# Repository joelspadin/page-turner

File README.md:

# Page Turner

This is an STM32-based "keyboard" which maps a pair of foot pedals with 6.35 mm (1/4") phone jacks to left/right arrow keys (or any other two keys), designed for switching pages on a sheet music reader. It was designed to be as small as possible while still being hand-solderable.

# PCB

The [pcb](./pcb) folder contains a [KiCad](https://www.kicad.org/) project for the PCB. It requires 4 layers and a 1.6 mm thick PCB.

All parts are hand-solderable. I recommend starting from the USB port and working out from the center on the top side, then soldering the phone jacks last.

With [Python](https://www.python.org/) and [Docker](https://www.docker.com/products/docker-desktop/) installed, you can use [KiBot](https://github.com/INTI-CMNB/KiBot) to generate Gerber files for JLC PCB or PCBWay. Simply run the [kibot.py](./kibot.py) script, then check the "out" folder for the results.

## Bill of Materials

| References | Part              | Manufacturer       | Package  | Qty. | Description           |
| ---------- | ----------------- | ------------------ | -------- | ---- | --------------------- |
| C5         | 10n capacitor     |                    | 0603     | 1    | SMT Ceramic capacitor |
| C3, C7     | 100n capacitor    |                    | 0603     | 2    | SMT Ceramic capacitor |
| C1, C2, C6 | 1u capacitor      |                    | 0603     | 3    | SMT Ceramic capacitor |
| C4         | 4.7u capacitor    |                    | 0603     | 1    | SMT Ceramic capacitor |
| R1, R2     | 5.1k resistor     |                    | 0603     | 2    | SMT resistor          |
| R3         | 10k resistor      |                    | 0603     | 1    | SMT resistor          |
| D1, D2     | SD03C-7           | Diodes Inc.        | SOD-323  | 2    | TVS diode             |
| D3         | PRTR5V0U2X,215    | Nexperia           | SOT-143  | 1    | TVS diode             |
| U1         | STM32F042F6P6TR   | STMicroelectronics | TSSOP-20 | 1    | ARM microcontroller   |
| U2         | TPS7A0533PDBVR    | Texas Instruments  | SOT-23-5 | 1    | 3.3V regulator        |
| SW1, SW2   | B3U-1000P-B       | Omron              |          | 2    | Tactile switch        |
| J1, J2     | NJ2FD-V           | Neutrik            |          | 2    | 6.35 mm phone jack    |
| J3         | USB4145-03-0170-C | GCT                |          | 1    | USB-C connector       |

D1, D2, and D3 are optional. They provide some ESD protection.

U2 may be substituted with any other 3.3V regulator that takes 5V input and uses the same footprint and pinout, e.g. TPS7A0333PDBVR.

# Firmware

The [src](./src) folder contains an Arduino sketch. It can be modified as necessary to change the two keys or if your foot pedals are normally closed instead of normally open.

You will need a SWD programmer such as a J-Link. I used a [Nordic nRF5340 DK](https://www.nordicsemi.com/Products/Development-hardware/nRF5340-DK). Other programmers such as a Black Magic Probe or STLink may work, but I have not tested these. Flashing instructions below assume using a J-Link.

There are pads for a Tag-Connect TC2030 "no legs" cable, or you can use the five pads at the top of the PCB to connect your programmer (note that these have 2 mm spacing instead of 2.54 mm due to size constraints).

To compile and flash the firmware:

1. Install [STM32CubeProgrammer](https://www.st.com/en/development-tools/stm32cubeprog.html)
2. Install and open [Arduino IDE](https://www.arduino.cc/en/software)
3. Install the [Arduino core for STM32](https://github.com/stm32duino/Arduino_Core_STM32/wiki/Getting-Started)
4. Open [src/page_turner.ino](./src/page_turner.ino) in Arduino IDE
5. Select **Tools > Board > STM32 MCU based boards > Generic STM32F0 series**
6. Select **Tools > Board part number > Generif F042F6Px**
7. Select **Tools > USB support (if available) > HID (keyboard and mouse)**
8. Select **Tools > Upload method > STM32CubeProgrammer (J-Link)**
9. Plug the PCB to USB power and connect your programmer to it.
10. Select **Sketch > Upload Using Programmer**

I ran into an issue where, after being flashed with Arduino firmware, STM32CubeProgrammer was unable to identify the board afterwards. To fix this, you can run STM32CubeProgrammer and try to connect. This will fail and ask you to select the type of processor. Select Cortex M0 to finish connecting. Run a full chip erase, then disconnect, and you will be able to flash again.

## Enclosure

The [enclosure](./enclosure) folder contains CAD files that can be used to create a 3D printed enclosure.

## Bill of Materials

| Part                                        | Qty. |
| ------------------------------------------- | ---- |
| [Back](./enclosure/Back.3mf) (3D printed)   | 1    |
| [Front](./enclosure/Front.3mf) (3D printed) | 1    |
| M2 x 3 mm heat-set insert                   | 4    |
| M2 x 5 mm counersunk screw                  | 4    |

## Assembly

1. Using a soldering iron, install the four heat set inserts into the holes in the back piece.

2. Place the PCB assembly into the back piece. The longer side of the PCB should line up with side of the back piece containing the heat-set inserts.

3. Press the caps into the 6.35 mm phone jacks and rotate them clockwise to lock them into place.
4. Slide the front piece on, lining up the four holes with the heat set inserts.

5. Install the four screws.

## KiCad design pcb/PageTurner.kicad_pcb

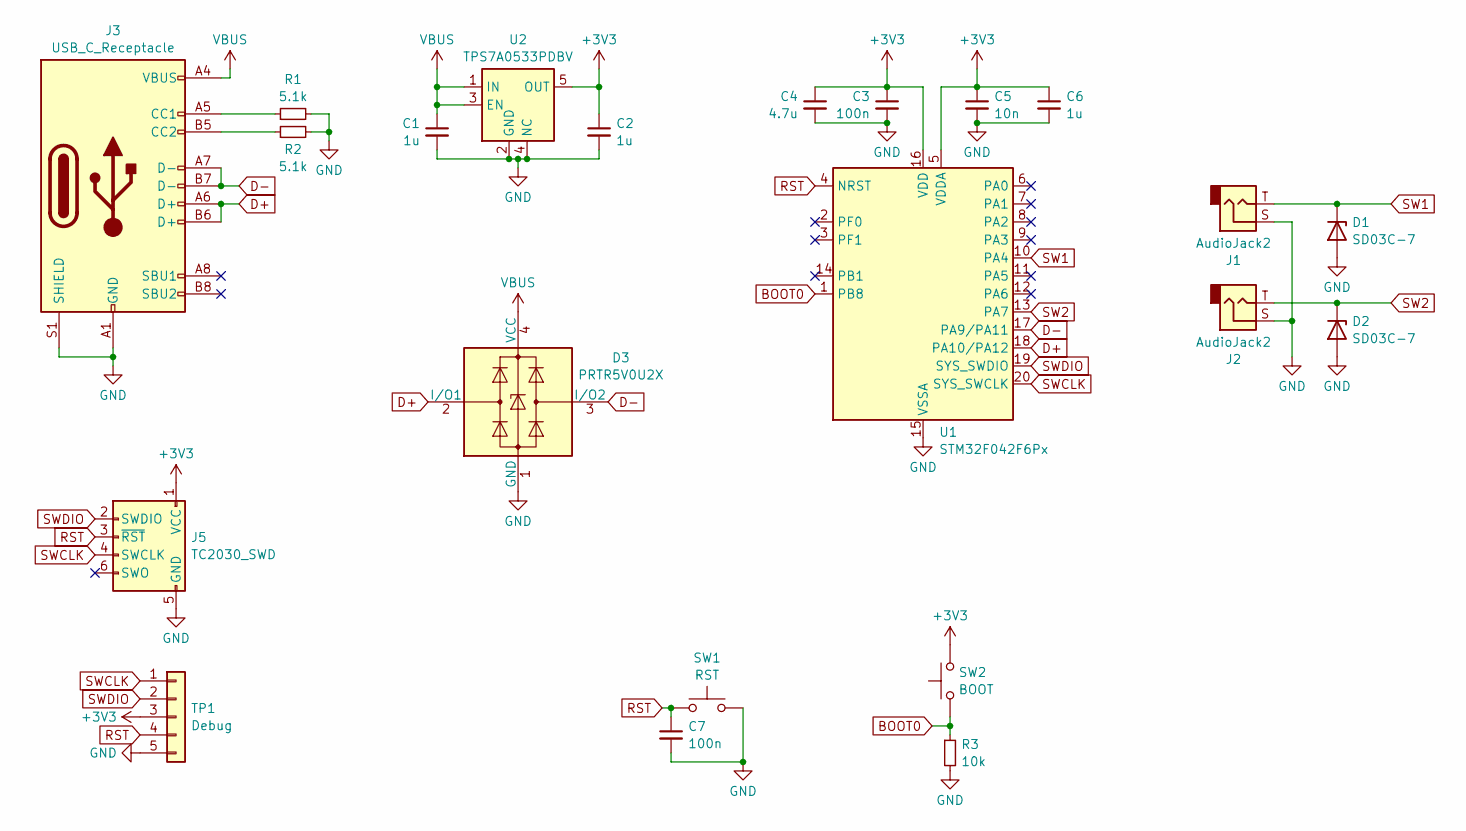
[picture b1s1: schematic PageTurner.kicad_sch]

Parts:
C1, C2, C6: 1u; C_0603_1608Metric_Pad1.08x0.95mm_HandSolder
C3, C7: 100n; C_0603_1608Metric_Pad1.08x0.95mm_HandSolder
C4: 4.7u; C_0603_1608Metric_Pad1.08x0.95mm_HandSolder
C5: 10n; C_0603_1608Metric_Pad1.08x0.95mm_HandSolder
D1, D2: SD03C-7; D_SOD-323_HandSoldering; Manufacturer Part Number SD03C-7
D3: PRTR5V0U2X; SOT-143; Manufacturer Part Number PRTR5V0U2X,215
J1, J2: AudioJack2; Jack_6.35mm_Neutrik_NJ2FD-V_Vertical; Manufacturer Part Number NJ2FD-V
J3: USB_C_Receptacle; USB_C_Receptacle_GCT_USB_4145; Manufacturer Part Number DX07S024WJ3R400
J5: TC2030_SWD; Tag-Connect_TC2030-IDC-NL_2x03_P1.27mm_Vertical
R1, R2: 5.1k; R_0603_1608Metric_Pad0.98x0.95mm_HandSolder
R3: 10k; R_0603_1608Metric_Pad0.98x0.95mm_HandSolder
SW1: RST; SW_SPST_B3U-1000P-B; Manufacturer Part Number B3U-1100P-B
SW2: BOOT; SW_SPST_B3U-1000P-B; Manufacturer Part Number B3U-1100P-B
TP1: Debug; PinHeader_1x05_P2.00mm_Vertical
U1: STM32F042F6Px; TSSOP-20_4.4x6.5mm_P0.65mm; Manufacturer Part Number STM32F042F6P6TR
U2: TPS7A0533PDBV; SOT-23-5; Manufacturer Part Number TPS7A0333PDBVR

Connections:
+3V3: C2.1, C3.1, C4.1, C5.1, C6.1, J5.1 (VCC), SW2.2, TP1.3, U1.5 (VDDA), U1.16 (VDD), U2.5 (OUT)
BOOT0: R3.1, SW2.1, U1.1 (PB8)
D+: D3.2 (I/O1), J3.A6 (D+), J3.B6 (D+), U1.18 (PA10/PA12)
D-: D3.3 (I/O2), J3.A7 (D-), J3.B7 (D-), U1.17 (PA9/PA11)
GND: C1.2, C2.2, C3.2, C4.2, C5.2, C6.2, C7.2, D1.2 (A), D2.2 (A), D3.1 (GND), J1.S, J2.S, J3.A1 (GND), J3.A12 (GND), J3.B1 (GND), J3.B12 (GND), J3.S1 (SHIELD), J5.5 (GND), R1.2, R2.2, R3.2, SW1.2, TP1.5, U1.15 (VSSA), U2.2 (GND), U2.4 (NC)
unnamed: J3.A5 (CC1), R1.1
unnamed: J3.B5 (CC2), R2.1
RST: C7.1, J5.3 (~RST), SW1.1, TP1.4, U1.4 (NRST)
SW1: D1.1 (K), J1.T, U1.10 (PA4)
SW2: D2.1 (K), J2.T, U1.13 (PA7)
SWCLK: J5.4 (SWCLK), TP1.1, U1.20 (SYS_SWCLK)
SWDIO: J5.2 (SWDIO), TP1.2, U1.19 (SYS_SWDIO)
VBUS: C1.1, D3.4 (VCC), J3.A4 (VBUS), J3.A9 (VBUS), J3.B4 (VBUS), J3.B9 (VBUS), U2.1 (IN), U2.3 (EN)

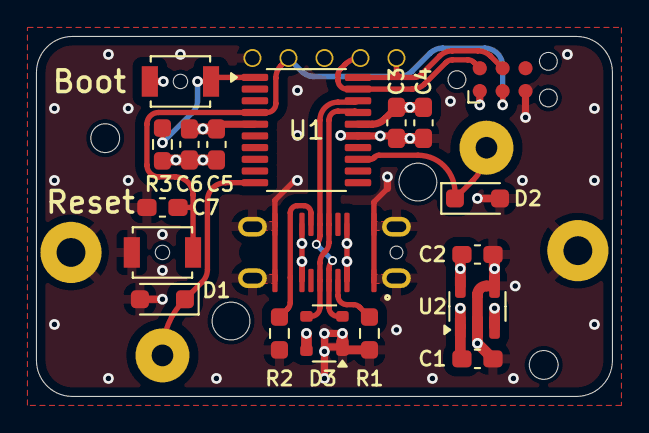
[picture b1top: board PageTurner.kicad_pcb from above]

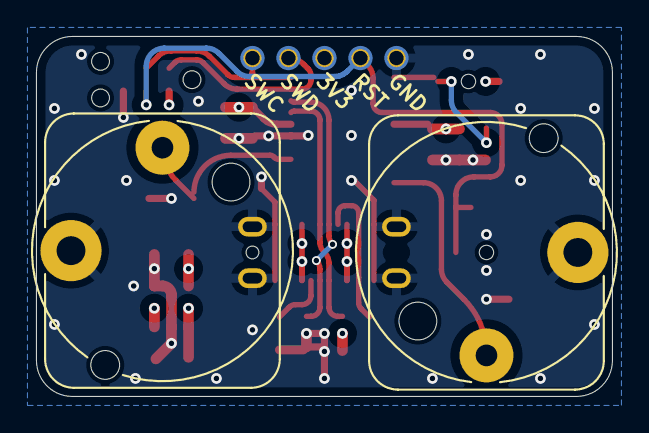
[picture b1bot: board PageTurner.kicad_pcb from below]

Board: 4 copper layers, 32.0 x 20.0 mm, 22 parts (3 on the bottom side), 13 nets.

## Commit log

2024-12-15 Add license
2024-12-15 Increase spacing between jacks slightly
2024-12-18 Update bom, fix decoupling capacitor value
2024-12-19 Add ESD diodes for pedal inputs
2024-12-19 Use cheaper ESD diode
2024-12-20 Use 1.6 mm PCB
2024-12-20 Switch to a cheaper and smaller USB connector
2025-01-02 Switch to 4 layers, add USB ESD diode
2025-01-02 Move USB ESD to top
2025-01-05 General cleanup
2025-03-15 Disconnect GPIOs from GND
    GPIOs are supposed to power up in floating input mode, so I tied some of
    them to GND for easier routing. For some reason the input voltage sagged
    to ~0.6 V until I disconnected these pins from the PCB though. I'm not
    sure if this was the cause or I just messed up soldering something, but
    disconnecting these just to be safe.
2025-03-16 Add code and 3D files, update README and LICENSE
    Added an Arduino sketch and updated the README with instructions for
    building and flashing it.
    Added 3D model files for the enclosure and updated the README with
    instructions for assembling it.
    Added a license for the Arduino sketch. Removed license information for
    footprints that were copied from another project but have been removed
2025-03-16 Fix dockerfile for KiCad 9, add instructions
